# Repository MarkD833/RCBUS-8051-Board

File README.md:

# RCBUS-8051-Board

I've recently re-discovered some of the microprocessors and microcontrollers from my youth via the [RC2014 website](https://rc2014.co.uk/) and the numerous boards available on [Steve Cousins website](https://smallcomputercentral.com/).

The ecosystem is dominated by the Z80 processor and the various Z80 peripheral chips from that era along with the CP/M operating system which the hardware can run.

My introduction to computing started with an 8051 microcontroller and I've got an itch to have a go at putting together an 8051 design that will be compatible with the more open RCBus system. My background isn't hardware so apologies to the hardware designers for the horrors that I'm about to unleash!

# My 8051 RCBus offering
## The 8051 microcontroller
Whilst wanting to retain the retro experience, I wanted to skip the use of a UV eraser - as I don't have one! I initially settled on an ATMEL AT89C51RB2 device as it could be programmed by invoking an interal bootloader and using the free ATMEL FLIP software to program it in-circuit. For the most part it worked - with one HUGE gotcha!

It took me a while to figure it out but after re-reading the datasheet I discovered that there was a fuse bit that prohibited the device from executing code in external memory. The problem was that FLIP can't reprogram this bit to enable external program execution and a parallel programmer was required. My XGecu T48 programmer doesn't support the AT89C51RB2 and I wasn't about to purchase a new PROM programmer just to program this chip.

After searching for a suitable alternative device, I settled on the ATMEL AT89S8253 which is MCS51 compatible.

## External memory
I needed the ability to write to program memory to load code and I wanted to experiment to see if I could come up with a desgin that would be able to switch between the 8051's [Harvard architecture](https://en.wikipedia.org/wiki/Harvard_architecture) (where program memory and data memory are normally separate) and a [von Neumann architecture](https://en.wikipedia.org/wiki/Von_Neumann_architecture).

In order to have the maximum amount of code space and data space, I would need a 128K SRAM device.

## The RCBus
The RCBus supports both memory space and IO space. As I was going to have the maximum amout of addressable memory on-board, off-board memory space was not going to be supported. IO space is 256 bytes and is mapped into the data memory map.

# The design (so far...)
The design at v1.1 is shown in the image below. The board is hopefully the size of the RCBus "medium" module with a 40 pin edge connector as detailed in the [RCBus specification](https://smallcomputercentral.com/rcbus/) v1.0.

# Memory Map

After a hard reset, the lower 12K of program memory ($0000..$2FFF) resides inside the AT89S8253 as FLASH memory and the bulk of the 64K block of RAM is shared between program space and data space.

# What works
I've ported Dave Dunfields MON51 monitor program over to the 89S8253. Most of the work involved getting the code to assemble using ASEM-51 v1.3 under Windows 10. The modified MON51 (MON51.a51) and original (MON51.ASM) are in the MON51 folder.

Currently:
* MON51 appears to function correctly
* Program space and data space are shared on power up
* Code can be downloaded via MON51 into the shared RAM and executed
* The on-board latch (74LS259) can be written to ($F800..$FBFF)
* RCBus IO space can be accessed ($FC00..$FFFF)
* Program space and data space can be separated (write $01 to $F801)
* Internal reboot works - can execute code in external memory starting at address $0000
 
## RCBus boards
The following boards appear to function correctly with the 8051 micro:
* SC129 Digital I/O Board
* SC704 I2C Bus Master Board (inc SC406 temperature module)
* SC705 Serial ACIA Board
 
# Still to do
* Further checks on the RCBus IO space using a few of Steve Cousins boards

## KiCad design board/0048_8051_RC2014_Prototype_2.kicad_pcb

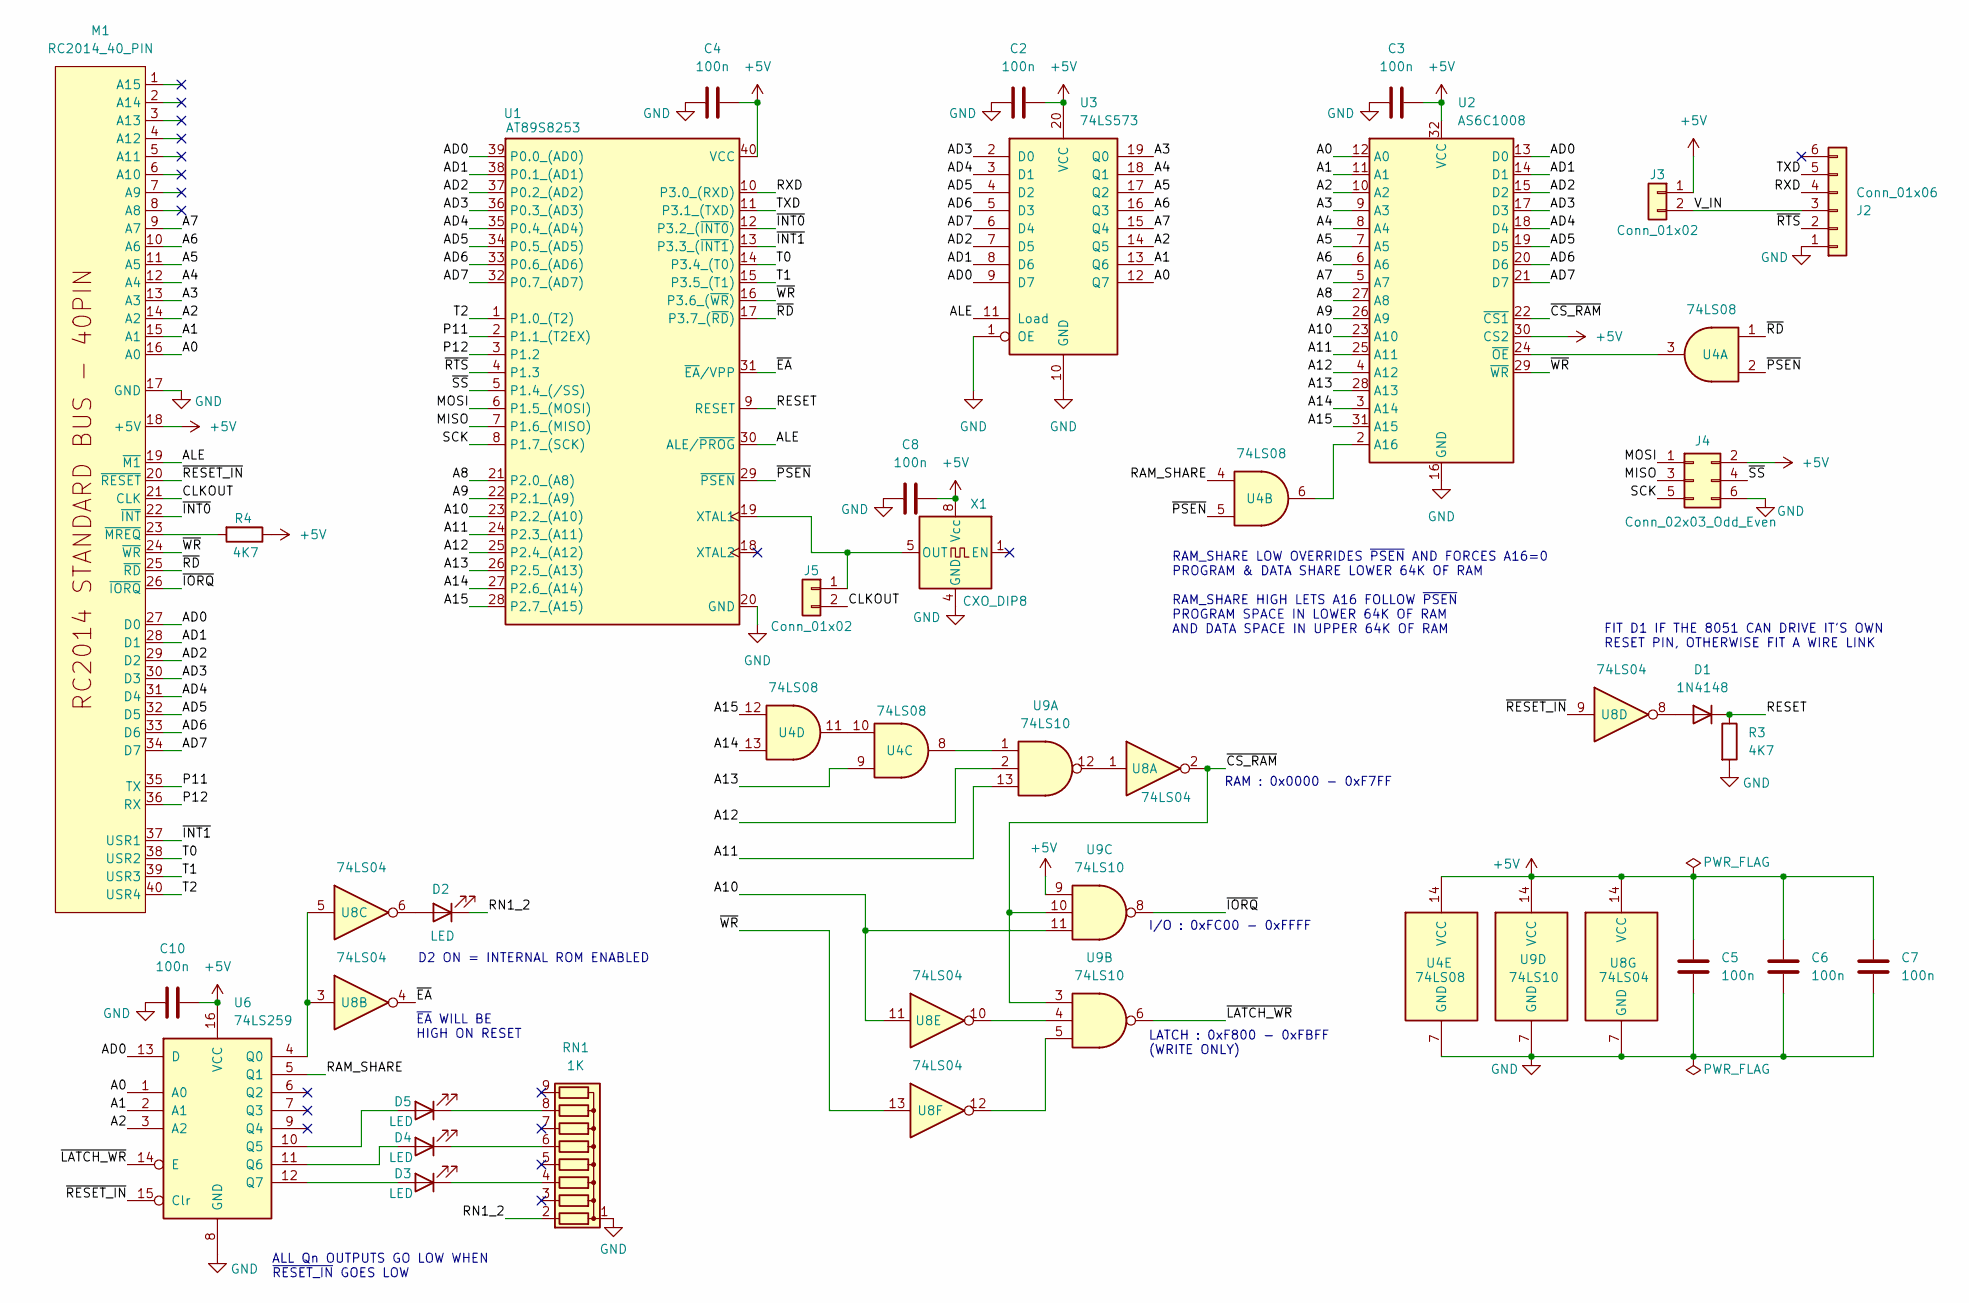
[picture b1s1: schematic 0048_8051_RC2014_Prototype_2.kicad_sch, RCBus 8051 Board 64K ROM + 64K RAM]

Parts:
C2, C3, C4, C5, C6, C7, C8, C10: 100n; C_Disc_D5.0mm_W2.5mm_P2.50mm
D1: 1N4148; D_DO-35_SOD27_P7.62mm_Horizontal
D2, D3, D4, D5: LED; LED_D3.0mm
J2: Conn_01x06; PinSocket_1x06_P2.54mm_Horizontal
J3, J5: Conn_01x02; PinHeader_1x02_P2.54mm_Vertical
J4: Conn_02x03_Odd_Even; PinHeader_2x03_P2.54mm_Horizontal
M1: RC2014_40_PIN; RCBUS_40P_MEDIUM
R3, R4: 4K7; R_Axial_DIN0207_L6.3mm_D2.5mm_P7.62mm_Horizontal
RN1: 1K; R_Array_SIP9
U1: AT89S8253; DIP-40_W15.24mm_Socket
U2: AS6C1008; DIP-32_W15.24mm_Socket
U3: 74LS573; DIP-20_W7.62mm_Socket
U4: 74LS08; DIP-14_W7.62mm_Socket
U6: 74LS259; DIP-16_W7.62mm_Socket
U8: 74LS04; DIP-14_W7.62mm_Socket
U9: 74LS10; DIP-14_W7.62mm_Socket
X1: CXO_DIP8; Oscillator_DIP-8

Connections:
+5V: C2.2, C3.2, C4.2, C5.1, C6.1, C7.1, C8.2, C10.2, J3.1, J4.2, M1.18 (+5V), R4.1, U1.40 (VCC), U2.30 (CS2), U2.32 (VCC), U3.20 (VCC), U4.14 (VCC), U6.16 (VCC), U8.14 (VCC), U9.9, U9.14 (VCC), X1.8 (Vcc)
/A0: M1.16 (A0), U2.12 (A0), U3.12 (Q7), U6.1 (A0)
/A1: M1.15 (A1), U2.11 (A1), U3.13 (Q6), U6.2 (A1)
/A2: M1.14 (A2), U2.10 (A2), U3.14 (Q5), U6.3 (A2)
/A3: M1.13 (A3), U2.9 (A3), U3.19 (Q0)
/A4: M1.12 (A4), U2.8 (A4), U3.18 (Q1)
/A5: M1.11 (A5), U2.7 (A5), U3.17 (Q2)
/A6: M1.10 (A6), U2.6 (A6), U3.16 (Q3)
/A7: M1.9 (A7), U2.5 (A7), U3.15 (Q4)
/A8: U1.21 (P2.0_(A8)), U2.27 (A8)
/A9: U1.22 (P2.1_(A9)), U2.26 (A9)
/A10: U1.23 (P2.2_(A10)), U2.23 (A10), U8.11, U9.11
/A11: U1.24 (P2.3_(A11)), U2.25 (A11), U9.13
/A12: U1.25 (P2.4_(A12)), U2.4 (A12), U9.2
/A13: U1.26 (P2.5_(A13)), U2.28 (A13), U4.9
/A14: U1.27 (P2.6_(A14)), U2.3 (A14), U4.13
/A15: U1.28 (P2.7_(A15)), U2.31 (A15), U4.12
/AD0: M1.27 (D0), U1.39 (P0.0_(AD0)), U2.13 (D0), U3.9 (D7), U6.13 (D)
/AD1: M1.28 (D1), U1.38 (P0.1_(AD1)), U2.14 (D1), U3.8 (D6)
/AD2: M1.29 (D2), U1.37 (P0.2_(AD2)), U2.15 (D2), U3.7 (D5)
/AD3: M1.30 (D3), U1.36 (P0.3_(AD3)), U2.17 (D3), U3.2 (D0)
/AD4: M1.31 (D4), U1.35 (P0.4_(AD4)), U2.18 (D4), U3.3 (D1)
/AD5: M1.32 (D5), U1.34 (P0.5_(AD5)), U2.19 (D5), U3.4 (D2)
/AD6: M1.33 (D6), U1.33 (P0.6_(AD6)), U2.20 (D6), U3.5 (D3)
/AD7: M1.34 (D7), U1.32 (P0.7_(AD7)), U2.21 (D7), U3.6 (D4)
/ALE: M1.19 (~M1), U1.30 (ALE/~PROG), U3.11 (Load)
/CLKOUT: J5.2, M1.21 (CLK)
/MISO: J4.3, U1.7 (P1.6_(MISO))
/MOSI: J4.1, U1.6 (P1.5_(MOSI))
/P11: M1.35 (TX), U1.2 (P1.1_(T2EX))
/P12: M1.36 (RX), U1.3 (P1.2)
/RAM_SHARE: U4.4, U6.5 (Q1)
/RESET: D1.1 (K), R3.1, U1.9 (RESET)
/RN1_2: D2.1 (K), RN1.2 (R1)
/RXD: J2.4, U1.10 (P3.0_(RXD))
/SCK: J4.5, U1.8 (P1.7_(SCK))
/T0: M1.38 (USR2), U1.14 (P3.4_(T0))
/T1: M1.39 (USR3), U1.15 (P3.5_(T1))
/T2: M1.40 (USR4), U1.1 (P1.0_(T2))
/TXD: J2.5, U1.11 (P3.1_(TXD))
/V_IN: J2.3, J3.2
/~CS_RAM: U2.22 (~CS1), U8.2, U9.3, U9.10
/~EA: U1.31 (~EA/VPP), U8.4
/~INT0: M1.22 (~INT), U1.12 (P3.2_(~INT0))
/~INT1: M1.37 (USR1), U1.13 (P3.3_(~INT1))
/~IORQ: M1.26 (~IORQ), U9.8
/~LATCH_WR: U6.14 (E), U9.6
/~PSEN: U1.29 (~PSEN), U4.2, U4.5
/~RD: M1.25 (~RD), U1.17 (P3.7_(~RD)), U4.1
/~RESET_IN: M1.20 (~RESET), U6.15 (Clr), U8.9
/~RTS: J2.2, U1.4 (P1.3)
/~SS: J4.4, U1.5 (P1.4_(/SS))
/~WR: M1.24 (~WR), U1.16 (P3.6_(~WR)), U2.29 (~WR), U8.13
GND: C2.1, C3.1, C4.1, C5.2, C6.2, C7.2, C8.1, C10.1, J2.1, J4.6, M1.17 (GND), R3.2, RN1.1 (common), U1.20 (GND), U2.16 (GND), U3.1 (OE), U3.10 (GND), U4.7 (GND), U6.8 (GND), U8.7 (GND), U9.7 (GND), X1.4 (GND)
unnamed: D1.2 (A), U8.8
unnamed: D2.2 (A), U8.6
unnamed: D3.2 (A), U6.12 (Q7)
unnamed: D3.1 (K), RN1.4 (R3)
unnamed: D4.2 (A), U6.11 (Q6)
unnamed: D4.1 (K), RN1.6 (R5)
unnamed: D5.2 (A), U6.10 (Q5)
unnamed: D5.1 (K), RN1.8 (R7)
unnamed: J5.1, U1.19 (XTAL1), X1.5 (OUT)
unnamed: M1.23 (~MREQ), R4.2
unnamed: U2.2 (A16), U4.6
unnamed: U2.24 (~OE), U4.3
unnamed: U4.8, U9.1
unnamed: U4.10, U4.11
unnamed: U6.4 (Q0), U8.3, U8.5
unnamed: U8.1, U9.12
unnamed: U8.10, U9.4
unnamed: U8.12, U9.5

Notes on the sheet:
ALL Qn OUTPUTS GO LOW WHEN ~{RESET_IN} GOES LOW
D2 ON = INTERNAL ROM ENABLED
RAM_SHARE LOW OVERRIDES ~{PSEN} AND FORCES A16=0 PROGRAM & DATA SHARE LOWER 64K OF RAM RAM_SHARE HIGH LETS A16 FOLLOW ~{PSEN} PROGRAM SPACE IN LOWER 64K OF RAM AND DATA SPACE IN UPPER 64K OF RAM
FIT D1 IF THE 8051 CAN DRIVE IT'S OWN RESET PIN, OTHERWISE FIT A WIRE LINK
~{EA} WILL BE HIGH ON RESET
I/O : 0xFC00 - 0xFFFF
LATCH : 0xF800 - 0xFBFF (WRITE ONLY)
RAM : 0x0000 - 0xF7FF

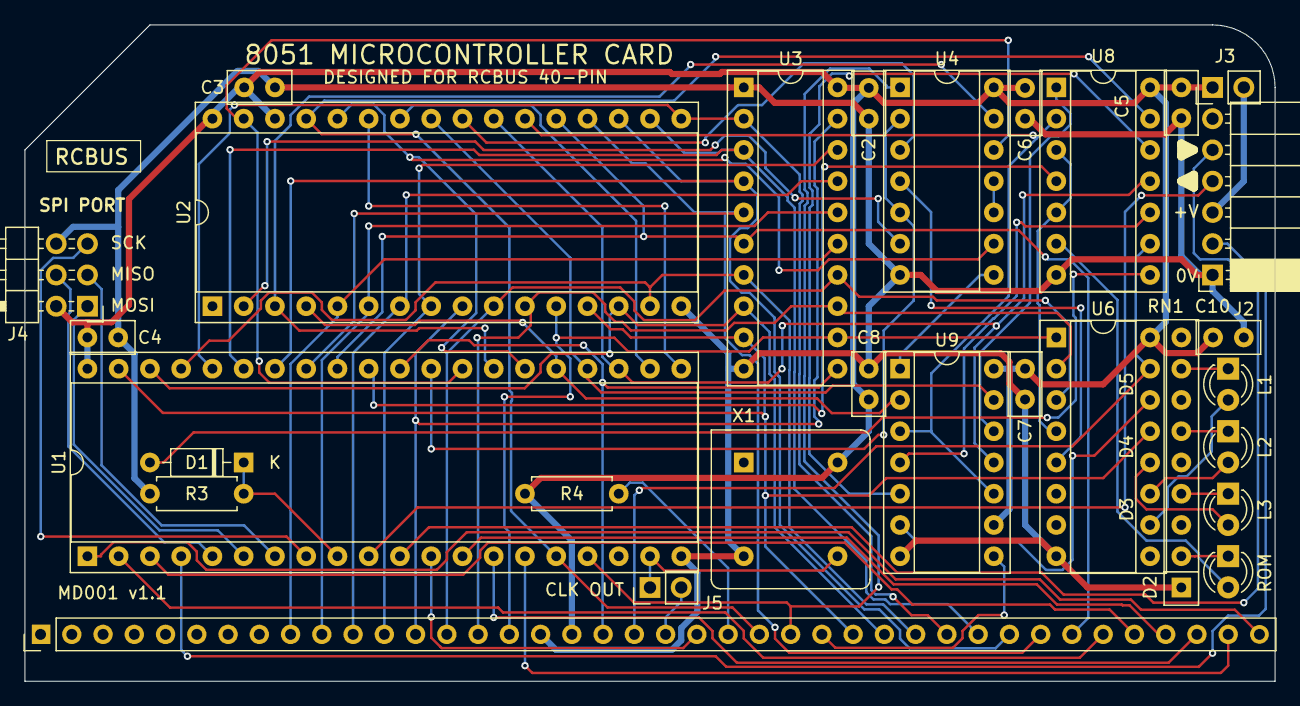
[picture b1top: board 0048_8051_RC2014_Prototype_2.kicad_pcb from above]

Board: 2 copper layers, 101.6 x 53.3 mm, 29 parts (0 on the bottom side), 72 nets.

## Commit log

2025-01-22 Startup
2025-01-22 added monitor
2025-01-23 added memory map
2025-01-24 added test code
2025-01-25 Updated MON51 and readme
2025-02-15 rearranged code folder
2025-02-16 added SC705 test code
